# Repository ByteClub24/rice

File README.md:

# rice
This should build a base for a robot kit

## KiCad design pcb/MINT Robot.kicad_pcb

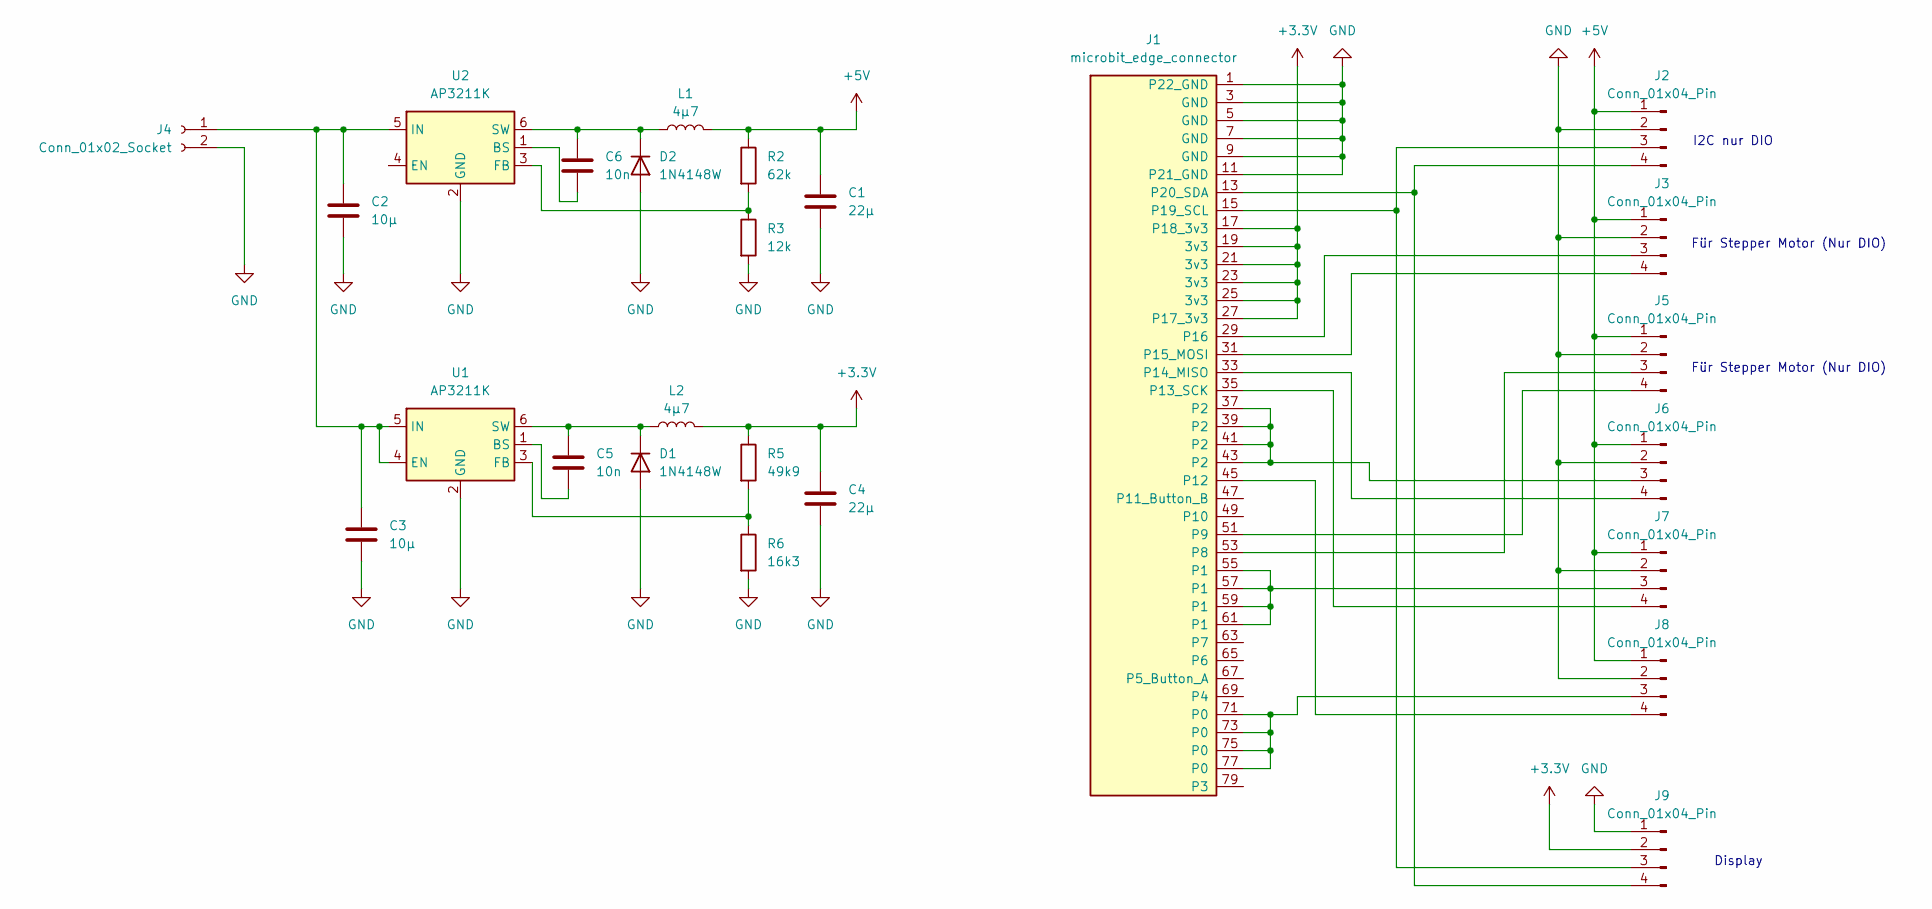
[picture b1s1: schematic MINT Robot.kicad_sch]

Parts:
C1, C4: 22µ; C_1206_3216Metric
C2, C3: 10µ; C_1206_3216Metric
C5, C6: 10n; C_1206_3216Metric
D1, D2: 1N4148W; D_SOD-123F
J1: microbit_edge_connector; 4UCON_10156_2x40_P1.27mm_Socket_Horizontal
J2, J3, J5, J6, J7, J8: Conn_01x04_Pin; JST_PH_S4B-PH-K_1x04_P2.00mm_Horizontal
J4: Conn_01x02_Socket; JST_PH_B2B-PH-K_1x02_P2.00mm_Vertical
J9: Conn_01x04_Pin; PinSocket_1x04_P2.54mm_Vertical
L1, L2: 4µ7; L_1210_3225Metric
R2: 62k; R_1206_3216Metric
R3: 12k; R_1206_3216Metric
R5: 49k9; R_1206_3216Metric
R6: 16k3; R_1206_3216Metric
U1, U2: AP3211K; AO_AOZ666xDI_DFN-8-1EP_3x3mm_P0.65mm_EP1.25x2.7mm

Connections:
+3.3V: C4.1, J1.17 (P18_3v3), J1.19 (3v3), J1.21 (3v3), J1.23 (3v3), J1.25 (3v3), J1.27 (P17_3v3), J9.2, L2.2, R5.1
+5V: C1.1, J2.1, J3.1, J5.1, J6.1, J7.1, J8.1, L1.2, R2.1
GND: C1.2, C2.2, C3.2, C4.2, D1.2 (A), D2.2 (A), J1.1 (P22_GND), J1.3 (GND), J1.5 (GND), J1.7 (GND), J1.9 (GND), J1.11 (P21_GND), J2.2, J3.2, J4.2, J5.2, J6.2, J7.2, J8.2, J9.1, R3.2, R6.2, U1.2 (GND), U2.2 (GND)
unnamed: C5.1, D1.1 (K), L2.1, U1.6 (SW)
unnamed: C6.1, D2.1 (K), L1.1, U2.6 (SW)
unnamed: J1.53 (P8), J5.3
unnamed: J1.51 (P9), J5.4
unnamed: J1.45 (P12), J8.4
unnamed: J1.35 (P13_SCK), J7.4
unnamed: J1.33 (P14_MISO), J6.4
unnamed: J1.31 (P15_MOSI), J3.4
unnamed: J1.29 (P16), J3.3
unnamed: J1.15 (P19_SCL), J2.3, J9.3
unnamed: J1.13 (P20_SDA), J2.4, J9.4
unnamed: C2.1, C3.1, J4.1, U1.4 (EN), U1.5 (IN), U2.5 (IN)
unnamed: J1.37 (P2), J1.39 (P2), J1.41 (P2), J1.43 (P2), J6.3
unnamed: J1.55 (P1), J1.57 (P1), J1.59 (P1), J1.61 (P1), J7.3
unnamed: J1.71 (P0), J1.73 (P0), J1.75 (P0), J1.77 (P0), J8.3
unnamed: C5.2, U1.1 (BS)
unnamed: R5.2, R6.1, U1.3 (FB)
unnamed: C6.2, U2.1 (BS)
unnamed: R2.2, R3.1, U2.3 (FB)

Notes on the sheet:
Für Stepper Motor (Nur DIO)
I2C nur DIO
Display

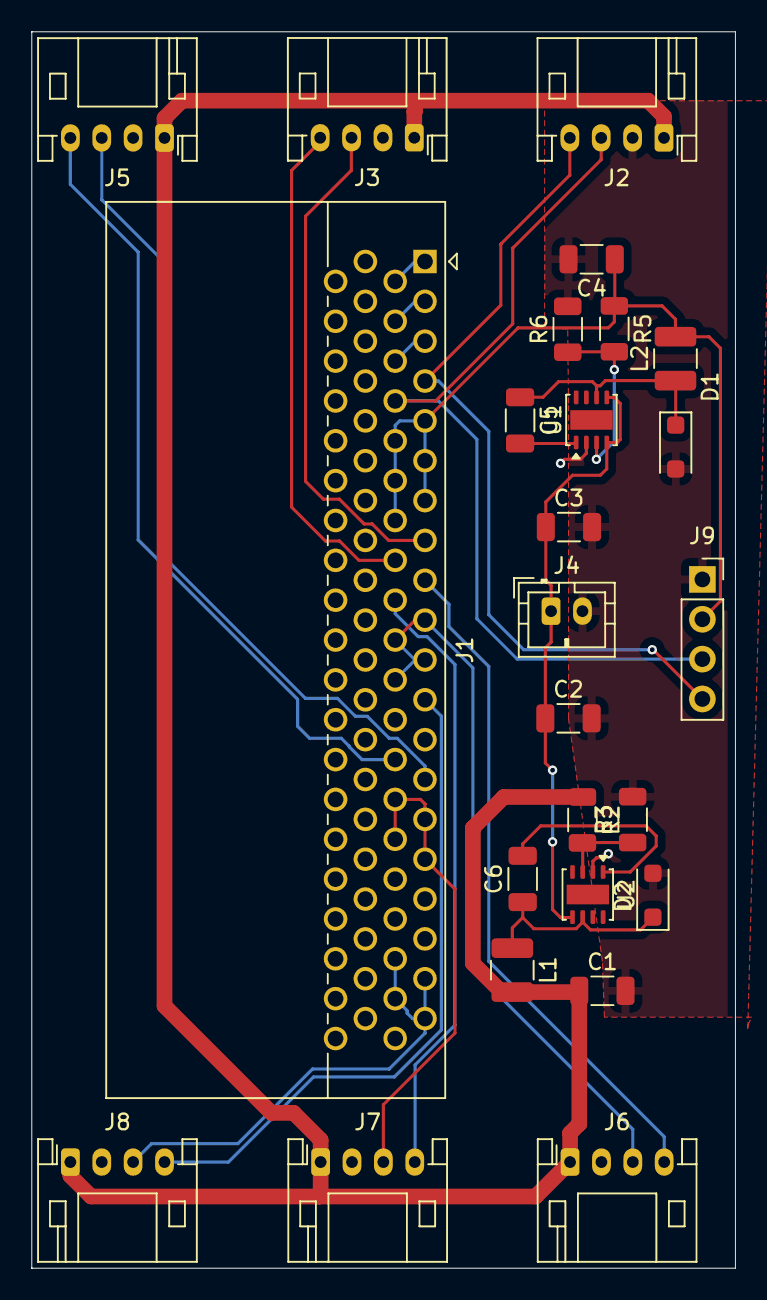
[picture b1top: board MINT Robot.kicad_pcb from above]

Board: 2 copper layers, 44.9 x 78.8 mm, 25 parts (0 on the bottom side), 22 nets.

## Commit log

2026-03-10 Add pcb design v1
